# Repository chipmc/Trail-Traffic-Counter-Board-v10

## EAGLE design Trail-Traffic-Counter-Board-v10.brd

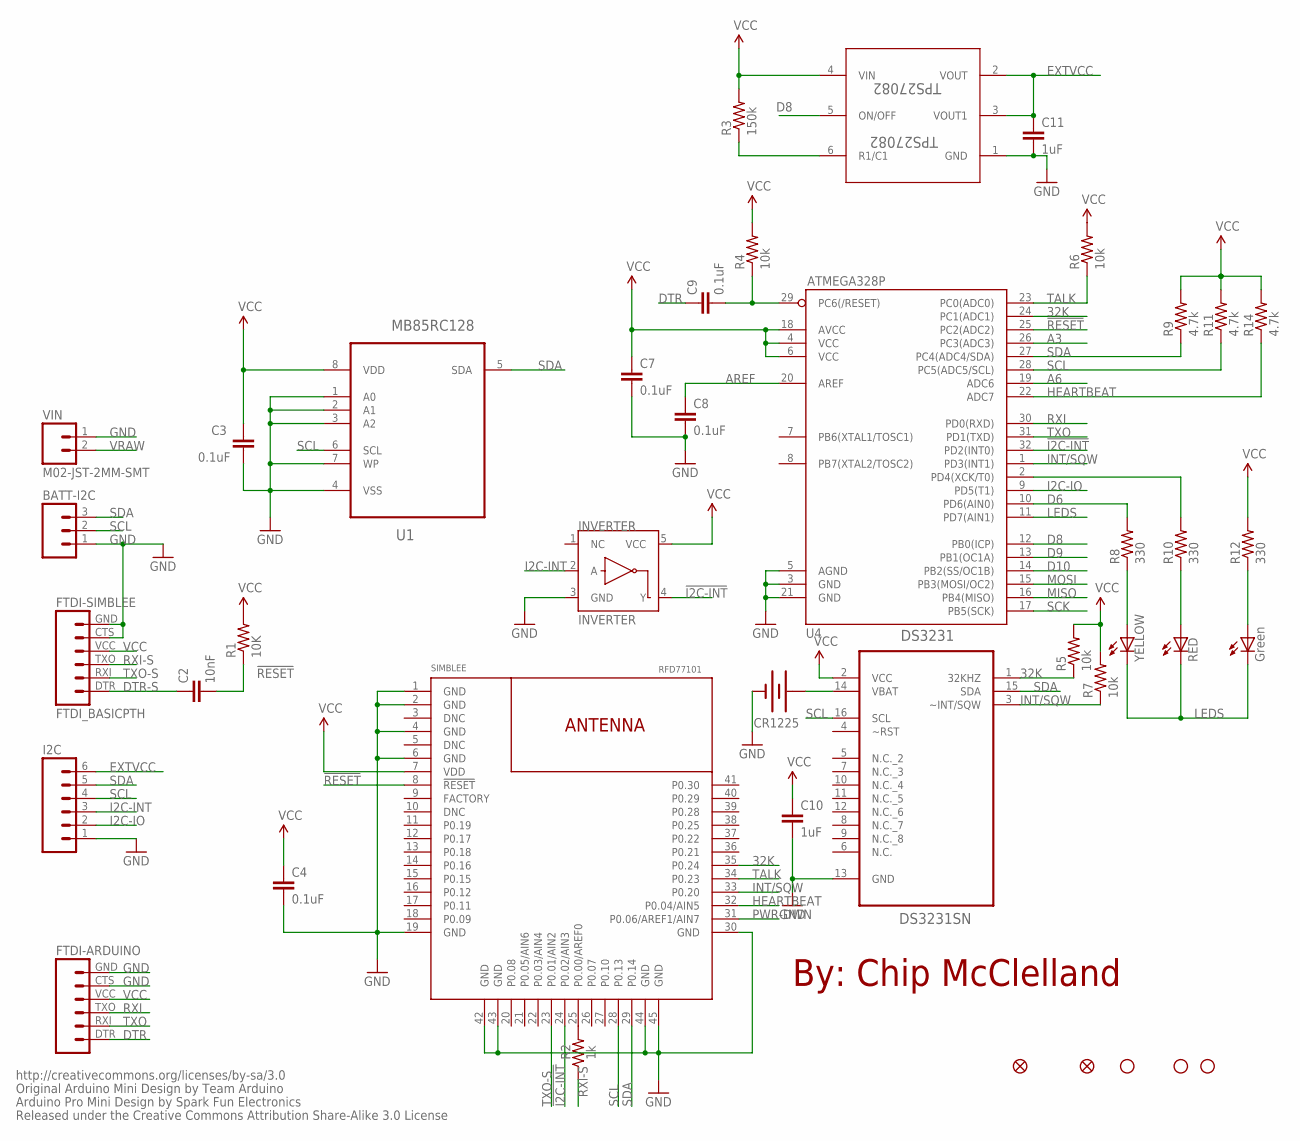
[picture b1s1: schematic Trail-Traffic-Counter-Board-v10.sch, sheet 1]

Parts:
ATMEGA328P: U4; TQFP32-08
BATT-I2C: M03LOCK; 1X03_LOCK
C2: 10nF; 0805
C3, C4, C7, C8, C9: 0.1uF; 0805
C10, C11: 1uF; 0805
CR1225: BATTERY12MM; BATTCON_12MM
DS3231: DS3231SN; SOIC127P1032X265-16N
FID1, FID2: FIDUCIALUFIDUCIAL; MICRO-FIDUCIAL
FTDI-ARDUINO: FTDI Basic; FTDI_BASIC
FTDI-SIMBLEE: FTDI_BASICPTH; FTDI_BASIC
I2C: M06LOCK; 1X06_LOCK
INVERTER: INVERTER; SOT23-5
JP6, JP7, JP8: STAND-OFF
LED1: YELLOW; CHIPLED_0805
LED2: RED; CHIPLED_0805
MB85RC128: U1; SOIC127P600X175-8N
PWR: Green; CHIPLED_0805
R1: 10K; 0805
R2: 1k; 0805
R3: 150k; 0805
R4, R5, R6, R7: 10k; 0805
R8, R10, R12: 330; 0603-RES
R9, R11, R14: 4.7k; 0805
SIMBLEE: RFD77101
TPS27082: TPS27082; TSOT-23
VIN: M02-JST-2MM-SMT; JST-2-SMD

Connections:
32K: ATMEGA328P.24 (PC1(ADC1)), DS3231.1 (32KHZ), R5.1, SIMBLEE.35 (P0.24)
!I2C-INT: ATMEGA328P.32 (PD2(INT0)), INVERTER.4 (Y), SIMBLEE.24 (P0.02/AIN3)
!RESET: ATMEGA328P.25 (PC2(ADC2)), C2.2, R1.1, SIMBLEE.8 (!RESET!)
A3: ATMEGA328P.26 (PC3(ADC3))
A6: ATMEGA328P.19 (ADC6)
AREF: ATMEGA328P.20 (AREF), C8.1
D6: ATMEGA328P.10 (PD6(AIN0)), R8.2
D8: ATMEGA328P.12 (PB0(ICP)), TPS27082.5 (ON/OFF)
D9: ATMEGA328P.13 (PB1(OC1A))
D10: ATMEGA328P.14 (PB2(SS/OC1B))
DTR: C9.1, FTDI-ARDUINO.DTR (1)
DTR-S: C2.1, FTDI-SIMBLEE.DTR (1)
EXTVCC: C11.1, I2C.6, TPS27082.2 (VOUT), TPS27082.3 (VOUT1)
GND: ATMEGA328P.3 (GND), ATMEGA328P.5 (AGND), ATMEGA328P.21 (GND), BATT-I2C.1, C3.2, C4.2, C7.2, C8.2, C10.2, C11.2, CR1225.GND (-), DS3231.13 (GND), FTDI-ARDUINO.CTS (5), FTDI-ARDUINO.GND (6), FTDI-SIMBLEE.CTS (5), FTDI-SIMBLEE.GND (6), I2C.1, INVERTER.3 (GND), MB85RC128.1 (A0), MB85RC128.2 (A1), MB85RC128.3 (A2), MB85RC128.4 (VSS), MB85RC128.7 (WP), SIMBLEE.1 (GND), SIMBLEE.2 (GND), SIMBLEE.4 (GND), SIMBLEE.6 (GND), SIMBLEE.19 (GND), SIMBLEE.30 (GND), SIMBLEE.42 (GND), SIMBLEE.43 (GND), SIMBLEE.44 (GND), SIMBLEE.45 (GND), TPS27082.1 (GND), VIN.1 (2); also elsewhere on the board
HEARTBEAT: ATMEGA328P.22 (ADC7), R14.1, SIMBLEE.32 (P0.04/AIN5)
I2C-INT: I2C.3, INVERTER.2 (A)
I2C-IO: ATMEGA328P.9 (PD5(T1)), I2C.2
INT/SQW: ATMEGA328P.1 (PD3(INT1)), DS3231.3 (~INT/SQW), R7.1, SIMBLEE.33 (P0.20)
LEDS: ATMEGA328P.11 (PD7(AIN1)), LED1.C, LED2.C, PWR.C
MISO: ATMEGA328P.16 (PB4(MISO))
MOSI: ATMEGA328P.15 (PB3(MOSI/OC2))
unnamed: LED1.A, R8.1
unnamed: ATMEGA328P.2 (PD4(XCK/T0)), R10.2
unnamed: LED2.A, R10.1
unnamed: R3.1, TPS27082.6 (R1/C1)
unnamed: R2.2, SIMBLEE.25 (P0.00/AREF0)
unnamed: PWR.A, R12.1
PWR-DWN: SIMBLEE.31 (P0.06/AREF1/AIN7); also elsewhere on the board
RESET: ATMEGA328P.29 (PC6(/RESET)), C9.2, R4.1
RXI: ATMEGA328P.30 (PD0(RXD)), FTDI-ARDUINO.TXO (3)
RXI-S: FTDI-SIMBLEE.TXO (3), R2.1
SCK: ATMEGA328P.17 (PB5(SCK))
SCL: ATMEGA328P.28 (PC5(ADC5/SCL)), BATT-I2C.2, DS3231.16 (SCL), I2C.4, MB85RC128.6 (SCL), R11.1, SIMBLEE.28 (P0.13)
SDA: ATMEGA328P.27 (PC4(ADC4/SDA)), BATT-I2C.3, DS3231.15 (SDA), I2C.5, MB85RC128.5 (SDA), R9.1, SIMBLEE.29 (P0.14)
TALK: ATMEGA328P.23 (PC0(ADC0)), R6.1, SIMBLEE.34 (P0.23)
TXO: ATMEGA328P.31 (PD1(TXD)), FTDI-ARDUINO.RXI (2)
TXO-S: FTDI-SIMBLEE.RXI (2), SIMBLEE.23 (P0.01/AIN2)
VBAT: CR1225.PWR@1 (+), DS3231.14 (VBAT)
VCC: ATMEGA328P.4 (VCC), ATMEGA328P.6 (VCC), ATMEGA328P.18 (AVCC), C3.1, C4.1, C7.1, C10.1, DS3231.2 (VCC), FTDI-ARDUINO.VCC (4), FTDI-SIMBLEE.VCC (4), INVERTER.5 (VCC), MB85RC128.8 (VDD), R1.2, R3.2, R4.2, R5.2, R6.2, R7.2, R9.2, R11.2, R12.2, R14.2, SIMBLEE.7 (VDD), TPS27082.4 (VIN); also elsewhere on the board
VRAW: VIN.2 (1); also elsewhere on the board

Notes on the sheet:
Released under the Creative Commons Attribution Share-Alike 3.0 License
http://creativecommons.org/licenses/by-sa/3.0
Original Arduino Mini Design by Team Arduino
Arduino Pro Mini Design by Spark Fun Electronics
By: Chip McClelland

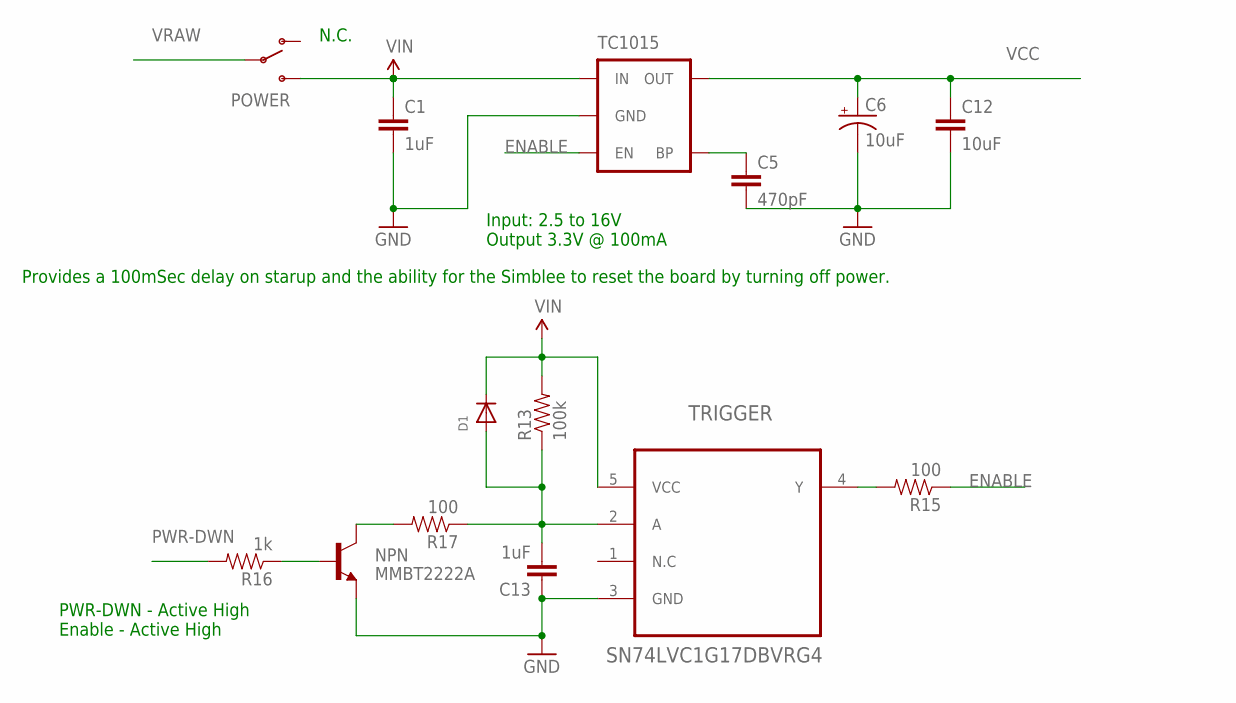
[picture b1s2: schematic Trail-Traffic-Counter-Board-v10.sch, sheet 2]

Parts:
C1, C13: 1uF; 0805
C5: 470pF; 0805
C6: 10uF; EIA3216
C12: 10uF; 0805
D1: DIODESOD-523; SOD-523
NPN: MMBT2222A; SOT23-3
POWER: SWITCH-SPDTPTH; SWITCH-SPDT
R13: 100k; 0805
R15, R17: 100; 0805
R16: 1k; 0805
TC1015: MIC52053.3V; SOT23-5
TRIGGER: SN74LVC1G17DBVRG4; SOT95P280X145-5N

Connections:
ENABLE: R15.1, TC1015.3 (EN)
GND: C1.2, C5.2, C6.C (-), C12.2, C13.1, NPN.2 (E), TC1015.2 (GND), TRIGGER.3 (GND); also elsewhere on the board
unnamed: C5.1, TC1015.4 (BP)
unnamed: C13.2, D1.A, R13.1, R17.1, TRIGGER.2 (A)
unnamed: R15.2, TRIGGER.4 (Y)
unnamed: NPN.1 (B), R16.1
unnamed: NPN.3 (C), R17.2
PWR-DWN: R16.2; also elsewhere on the board
VCC: C6.A (+), C12.1, TC1015.5 (OUT); also elsewhere on the board
VIN: C1.1, D1.K (C), POWER.3 (S), R13.2, TC1015.1 (IN), TRIGGER.5 (VCC)
VRAW: POWER.2; also elsewhere on the board

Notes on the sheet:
Input: 2.5 to 16V Output 3.3V @ 100mA
N.C.
PWR-DWN - Active High Enable - Active High
Provides a 100mSec delay on starup and the ability for the Simblee to reset the board by turning off power.

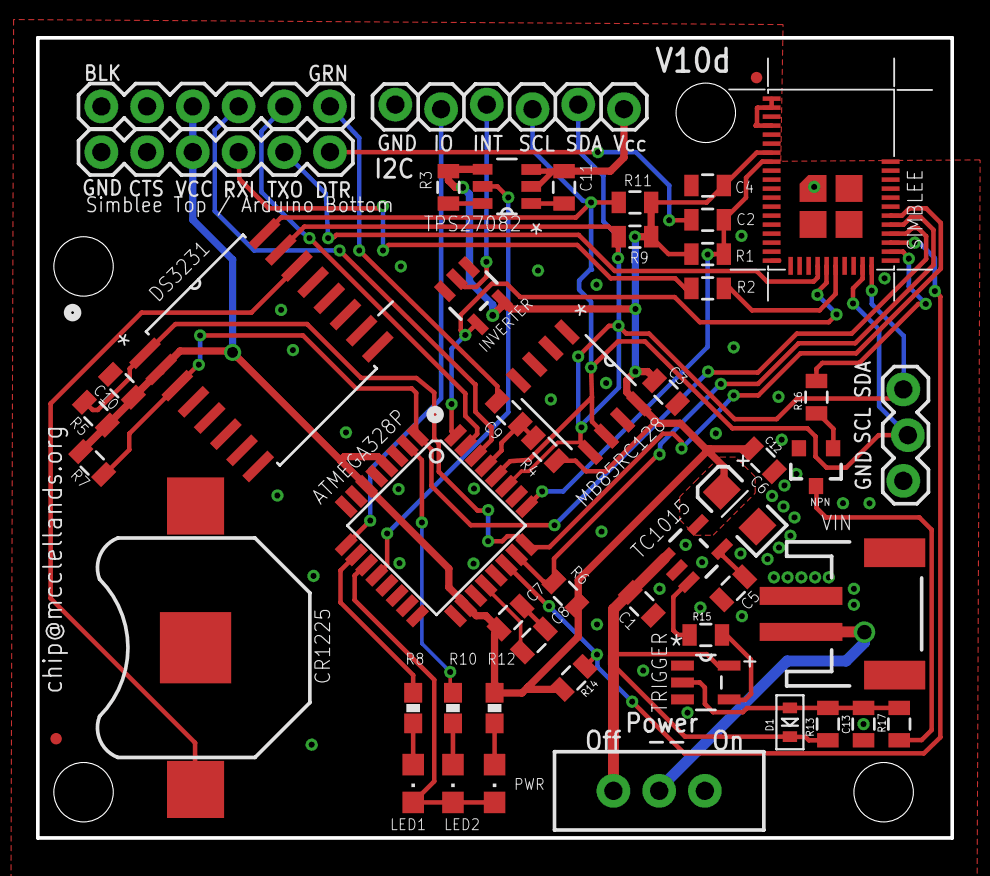
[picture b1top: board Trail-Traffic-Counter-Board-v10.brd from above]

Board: 2 copper layers, 50.8 x 44.5 mm, 56 parts (0 on the bottom side), 40 nets.

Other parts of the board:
JP2: STAND-OFF

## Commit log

2016-08-26 First Rev for v10
    v10 adds the ability to turn on an off the Vcc pin on the external i2c
    header.
2016-09-13 Updated the design to include an on-off for the external i2c port
2017-07-19 Latest Design

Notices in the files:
parts and their libraries:
SparkFun-Connectors: Licensing: CC v3.0 Share-Alike You are welcome to use this library for commercial purposes.
SparkFun-Resistors: Licensing: Creative Commons ShareAlike 4.0 International - https://creativecommons.org/licenses/by-sa/4.0
RFDigital: © 2015 RF Digital Corporation
